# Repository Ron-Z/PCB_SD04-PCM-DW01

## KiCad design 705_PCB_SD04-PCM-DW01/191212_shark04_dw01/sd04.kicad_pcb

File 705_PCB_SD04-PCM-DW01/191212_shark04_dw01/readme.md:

### Change log

v0.1 Draft release

v0.2 - 20200316

- 根据需求增加了 均衡指示灯
- 修改了部分不合理的布线。

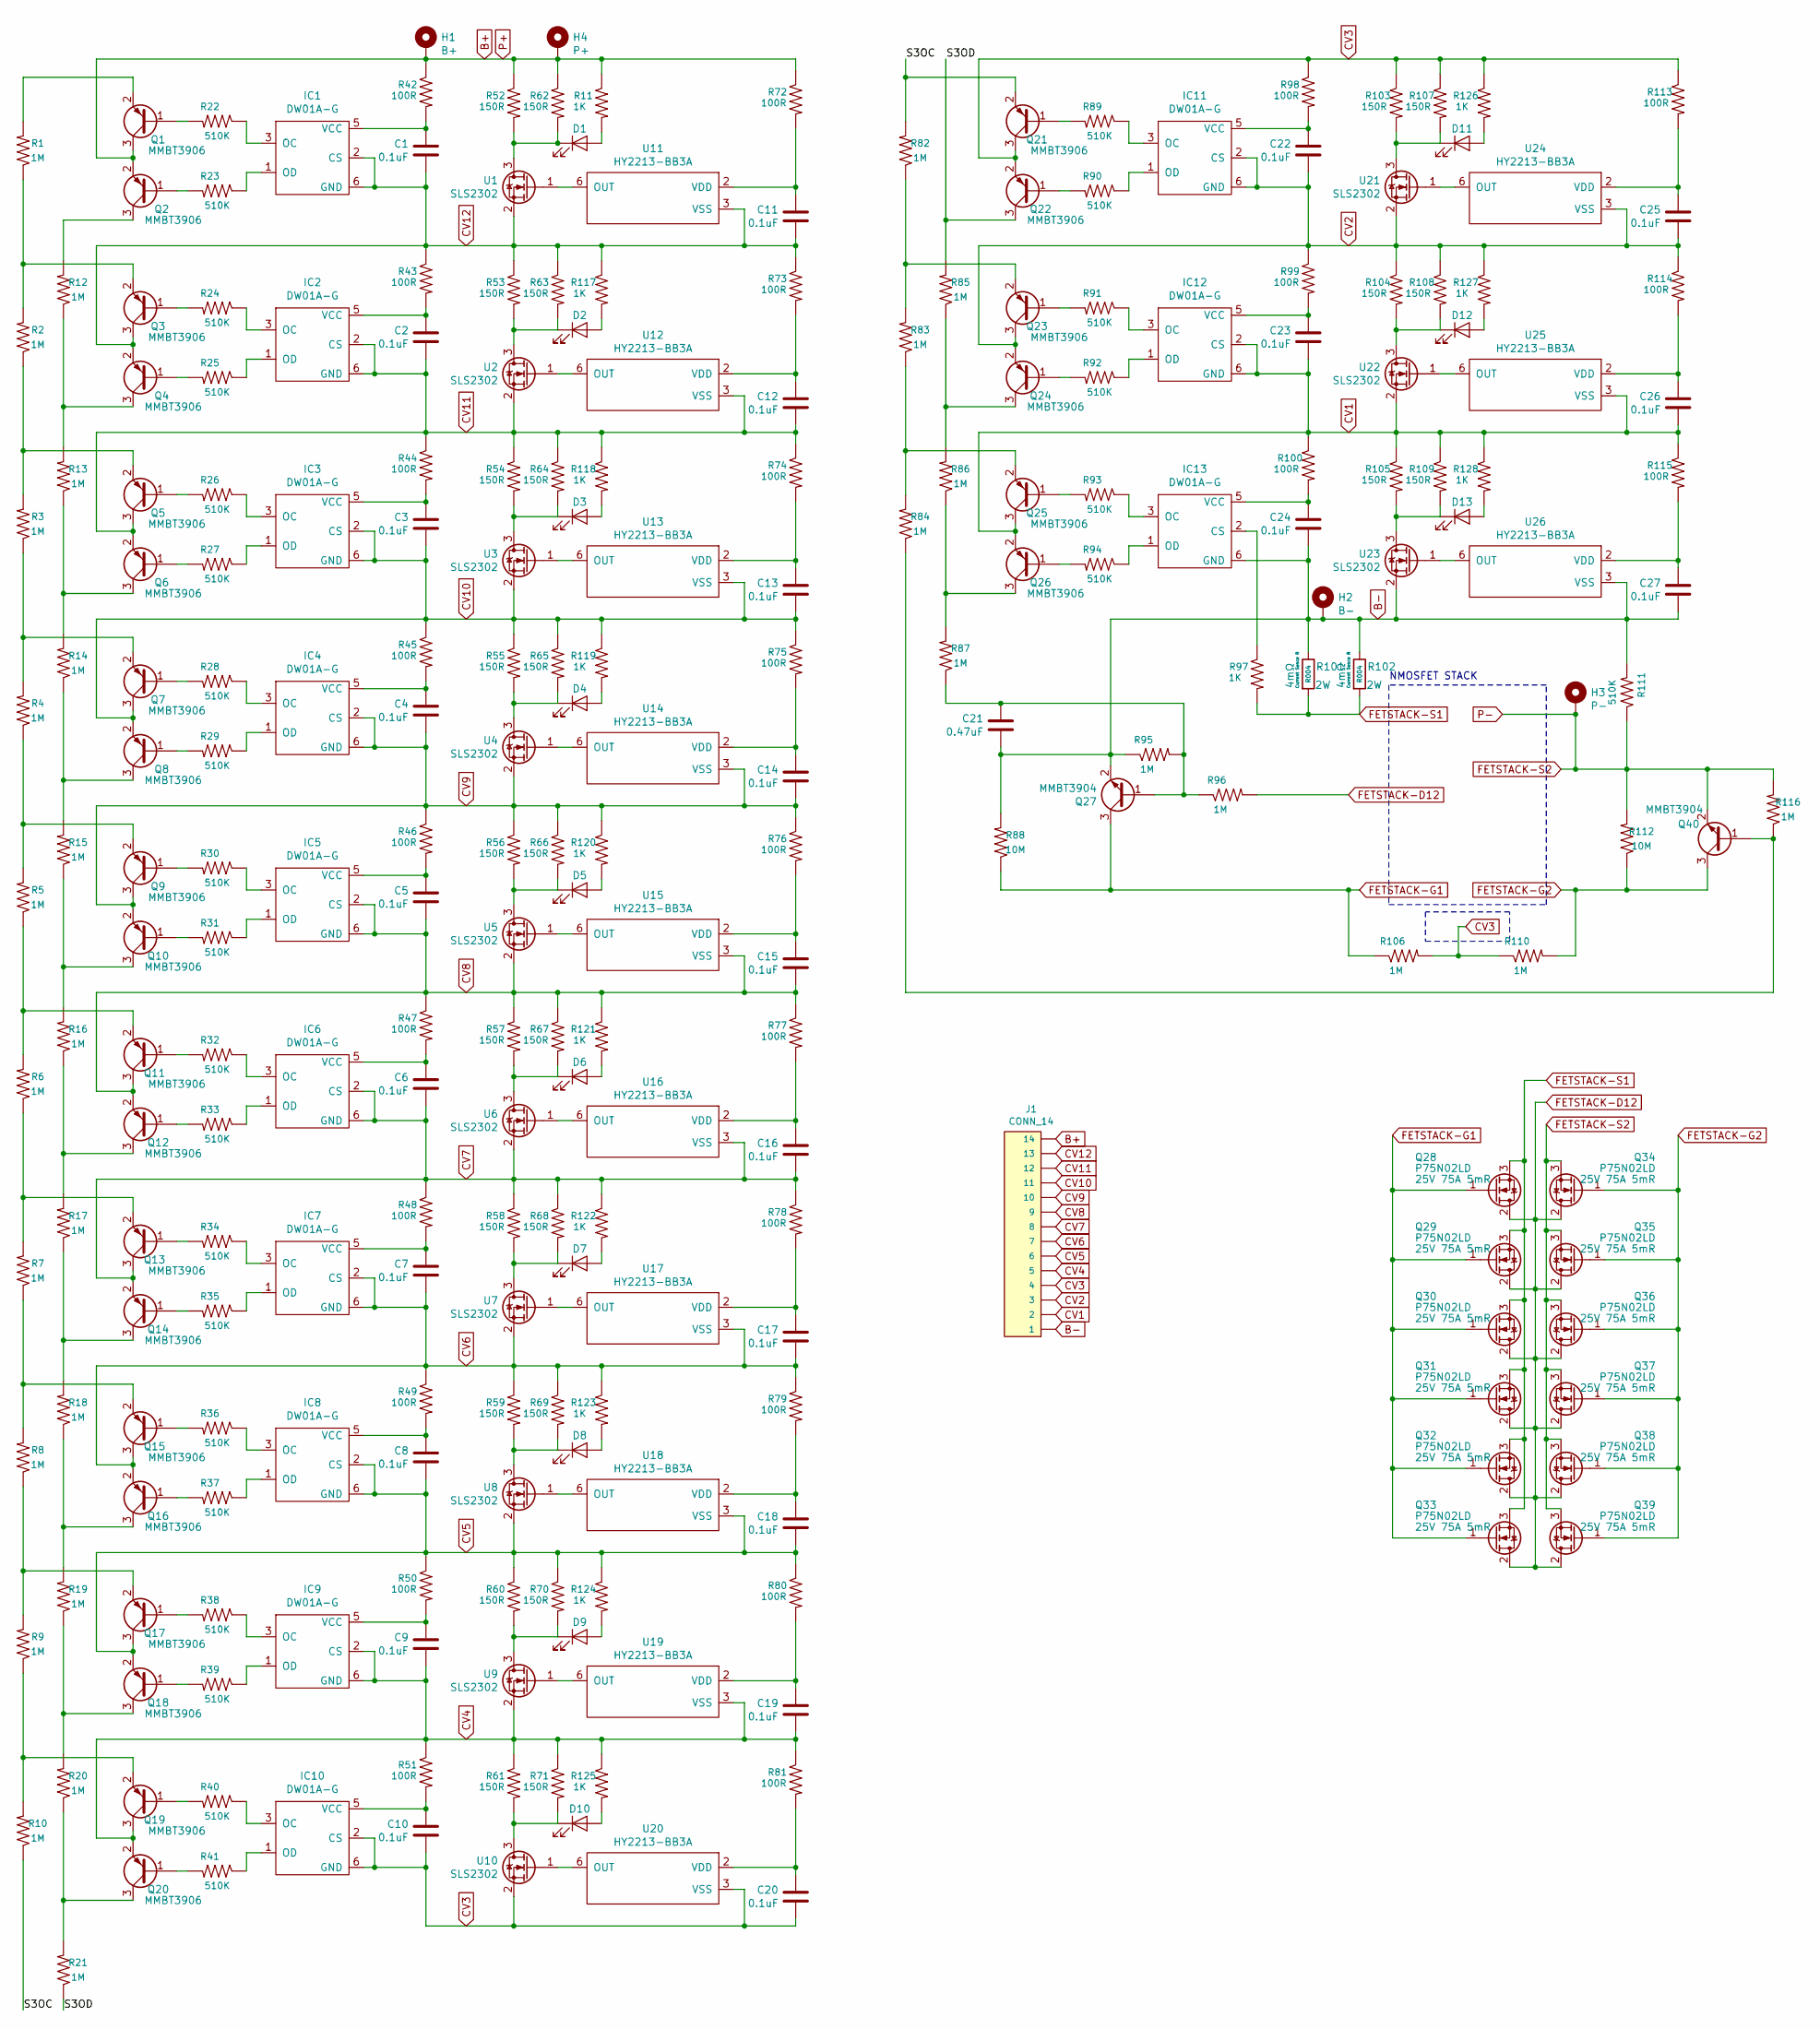
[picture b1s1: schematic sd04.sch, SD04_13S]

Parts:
C1, C2, C3, C4, C5, C6, C7, C8, C9, C10, C11, C12, C13, C14, C15, C16, C17, C18, C19, C20, C22, C23, C24, C25, C26, C27: 0.1uF; C_0603_1608Metric_Pad1.05x0.95mm_HandSolder
C21: 0.47uF; C_0603_1608Metric_Pad1.05x0.95mm_HandSolder
D1, D2, D3, D4, D5, D6, D7, D8, D9, D10, D11, D12, D13: LED; LED_0603_1608Metric_Pad1.05x0.95mm_HandSolder
H1: B+; SolderWirePad_1x01_SMD_5x5mm
H2: B-; SolderWirePad_1x01_SMD_5x5mm
H3: P-; SolderWirePad_1x01_SMD_5x5mm
H4: P+; SolderWirePad_1x01_SMD_5x5mm
IC1, IC2, IC3, IC4, IC5, IC6, IC7, IC8, IC9, IC10, IC11, IC12, IC13: DW01A-G; SOT-23-6_Handsoldering
J1: CONN_14; PinHeader_1x14_P2.54mm_Vertical
Q1, Q2, Q3, Q4, Q5, Q6, Q7, Q8, Q9, Q10, Q11, Q12, Q13, Q14, Q15, Q16, Q17, Q18, Q19, Q20, Q21, Q22, Q23, Q24, Q25, Q26: MMBT3906; SOT-23
Q27, Q40: MMBT3904; SOT-23
Q28, Q29, Q30, Q31, Q32, Q33, Q34, Q35, Q36, Q37, Q38, Q39: P75N02LD; TO-252-2
R1, R2, R3, R4, R5, R6, R7, R8, R9, R10, R12, R13, R14, R15, R16, R17, R18, R19, R20, R21, R82, R83, R84, R85, R86, R87, R95, R96, R106, R110, R116: 1M; R_0603_1608Metric_Pad1.05x0.95mm_HandSolder
R11, R97, R117, R118, R119, R120, R121, R122, R123, R124, R125, R126, R127, R128: 1K; R_0603_1608Metric_Pad1.05x0.95mm_HandSolder
R22, R23, R24, R25, R26, R27, R28, R29, R30, R31, R32, R33, R34, R35, R36, R37, R38, R39, R40, R41, R89, R90, R91, R92, R93, R94, R111: 510K; R_0603_1608Metric_Pad1.05x0.95mm_HandSolder
R42, R43, R44, R45, R46, R47, R48, R49, R50, R51, R72, R73, R74, R75, R76, R77, R78, R79, R80, R81, R98, R99, R100, R113, R114, R115: 100R; R_0603_1608Metric_Pad1.05x0.95mm_HandSolder
R52, R53, R54, R55, R56, R57, R58, R59, R60, R61, R62, R63, R64, R65, R66, R67, R68, R69, R70, R71, R103, R104, R105, R107, R108, R109: 150R; R_1206_3216Metric_Pad1.42x1.75mm_HandSolder
R88, R112: 10M; R_0603_1608Metric_Pad1.05x0.95mm_HandSolder
R101, R102: 4mΩ; R_2512_6332Metric_Pad1.52x3.35mm_HandSolder
U1, U2, U3, U4, U5, U6, U7, U8, U9, U10, U21, U22, U23: SLS2302; SOT-23
U11, U12, U13, U14, U15, U16, U17, U18, U19, U20, U24, U25, U26: HY2213-BB3A; SOT-23-6_Handsoldering

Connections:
/S3OC: Q21.2 (E), R10.1, R82.2
/S3OD: Q22.3 (C), R21.1, R85.2
B+: H1.1, H4.1, J1.14, Q1.3 (C), Q2.2 (E), R11.1, R42.1, R52.1, R62.1, R72.1
B-: C21.2, C24.2, C27.2, H2.1, IC13.6 (GND), J1.1, Q27.2 (E), R88.2, R95.1, R101.1, R102.1, R111.2, U23.2 (S), U26.3 (VSS)
CV1: C23.2, C26.2, IC12.2 (CS), IC12.6 (GND), J1.2, Q25.3 (C), Q26.2 (E), R100.1, R105.1, R109.1, R115.1, R128.1, U22.2 (S), U25.3 (VSS)
CV2: C22.2, C25.2, IC11.2 (CS), IC11.6 (GND), J1.3, Q23.3 (C), Q24.2 (E), R99.1, R104.1, R108.1, R114.1, R127.1, U21.2 (S), U24.3 (VSS)
CV3: C10.2, C20.2, IC10.2 (CS), IC10.6 (GND), J1.4, Q21.3 (C), Q22.2 (E), R98.1, R103.1, R106.2, R107.1, R110.1, R113.1, R126.1, U10.2 (S), U20.3 (VSS)
CV4: C9.2, C19.2, IC9.2 (CS), IC9.6 (GND), J1.5, Q19.3 (C), Q20.2 (E), R51.1, R61.1, R71.1, R81.1, R125.1, U9.2 (S), U19.3 (VSS)
CV5: C8.2, C18.2, IC8.2 (CS), IC8.6 (GND), J1.6, Q17.3 (C), Q18.2 (E), R50.1, R60.1, R70.1, R80.1, R124.1, U8.2 (S), U18.3 (VSS)
CV6: C7.2, C17.2, IC7.2 (CS), IC7.6 (GND), J1.7, Q15.3 (C), Q16.2 (E), R49.1, R59.1, R69.1, R79.1, R123.1, U7.2 (S), U17.3 (VSS)
CV7: C6.2, C16.2, IC6.2 (CS), IC6.6 (GND), J1.8, Q13.3 (C), Q14.2 (E), R48.1, R58.1, R68.1, R78.1, R122.1, U6.2 (S), U16.3 (VSS)
CV8: C5.2, C15.2, IC5.2 (CS), IC5.6 (GND), J1.9, Q11.3 (C), Q12.2 (E), R47.1, R57.1, R67.1, R77.1, R121.1, U5.2 (S), U15.3 (VSS)
CV9: C4.2, C14.2, IC4.2 (CS), IC4.6 (GND), J1.10, Q9.3 (C), Q10.2 (E), R46.1, R56.1, R66.1, R76.1, R120.1, U4.2 (S), U14.3 (VSS)
CV10: C3.2, C13.2, IC3.2 (CS), IC3.6 (GND), J1.11, Q7.3 (C), Q8.2 (E), R45.1, R55.1, R65.1, R75.1, R119.1, U3.2 (S), U13.3 (VSS)
CV11: C2.2, C12.2, IC2.2 (CS), IC2.6 (GND), J1.12, Q5.3 (C), Q6.2 (E), R44.1, R54.1, R64.1, R74.1, R118.1, U2.2 (S), U12.3 (VSS)
CV12: C1.2, C11.2, IC1.2 (CS), IC1.6 (GND), J1.13, Q3.3 (C), Q4.2 (E), R43.1, R53.1, R63.1, R73.1, R117.1, U1.2 (S), U11.3 (VSS)
FETSTACK-D12: Q28.2 (D), Q29.2 (D), Q30.2 (D), Q31.2 (D), Q32.2 (D), Q33.2 (D), Q34.2 (D), Q35.2 (D), Q36.2 (D), Q37.2 (D), Q38.2 (D), Q39.2 (D), R96.2
FETSTACK-G1: Q27.3 (C), Q28.1 (G), Q29.1 (G), Q30.1 (G), Q31.1 (G), Q32.1 (G), Q33.1 (G), R88.1, R106.1
FETSTACK-G2: Q34.1 (G), Q35.1 (G), Q36.1 (G), Q37.1 (G), Q38.1 (G), Q39.1 (G), Q40.3 (C), R110.2, R112.1
FETSTACK-S1: Q28.3 (S), Q29.3 (S), Q30.3 (S), Q31.3 (S), Q32.3 (S), Q33.3 (S), R97.2, R101.2, R102.2
FETSTACK-S2: H3.1, Q34.3 (S), Q35.3 (S), Q36.3 (S), Q37.3 (S), Q38.3 (S), Q39.3 (S), Q40.2 (E), R111.1, R112.2, R116.2
unnamed: C1.1, IC1.5 (VCC), R42.2
unnamed: C2.1, IC2.5 (VCC), R43.2
unnamed: C3.1, IC3.5 (VCC), R44.2
unnamed: C4.1, IC4.5 (VCC), R45.2
unnamed: C5.1, IC5.5 (VCC), R46.2
unnamed: C6.1, IC6.5 (VCC), R47.2
unnamed: C7.1, IC7.5 (VCC), R48.2
unnamed: C8.1, IC8.5 (VCC), R49.2
unnamed: C9.1, IC9.5 (VCC), R50.2
unnamed: C10.1, IC10.5 (VCC), R51.2
unnamed: C11.1, R72.2, U11.2 (VDD)
unnamed: C12.1, R73.2, U12.2 (VDD)
unnamed: C13.1, R74.2, U13.2 (VDD)
unnamed: C14.1, R75.2, U14.2 (VDD)
unnamed: C15.1, R76.2, U15.2 (VDD)
unnamed: C16.1, R77.2, U16.2 (VDD)
unnamed: C17.1, R78.2, U17.2 (VDD)
unnamed: C18.1, R79.2, U18.2 (VDD)
unnamed: C19.1, R80.2, U19.2 (VDD)
unnamed: C20.1, R81.2, U20.2 (VDD)
unnamed: C21.1, Q27.1 (B), R87.1, R95.2, R96.1
unnamed: C22.1, IC11.5 (VCC), R98.2
unnamed: C23.1, IC12.5 (VCC), R99.2
unnamed: C24.1, IC13.5 (VCC), R100.2
unnamed: C25.1, R113.2, U24.2 (VDD)
unnamed: C26.1, R114.2, U25.2 (VDD)
unnamed: C27.1, R115.2, U26.2 (VDD)
unnamed: D1.1 (K), R52.2, R62.2, U1.3 (D)
unnamed: D1.2 (A), R11.2
unnamed: D2.1 (K), R53.2, R63.2, U2.3 (D)
unnamed: D2.2 (A), R117.2
unnamed: D3.1 (K), R54.2, R64.2, U3.3 (D)
unnamed: D3.2 (A), R118.2
unnamed: D4.1 (K), R55.2, R65.2, U4.3 (D)
unnamed: D4.2 (A), R119.2
unnamed: D5.1 (K), R56.2, R66.2, U5.3 (D)
unnamed: D5.2 (A), R120.2
unnamed: D6.1 (K), R57.2, R67.2, U6.3 (D)
unnamed: D6.2 (A), R121.2
unnamed: D7.1 (K), R58.2, R68.2, U7.3 (D)
unnamed: D7.2 (A), R122.2
unnamed: D8.1 (K), R59.2, R69.2, U8.3 (D)
unnamed: D8.2 (A), R123.2
unnamed: D9.1 (K), R60.2, R70.2, U9.3 (D)
unnamed: D9.2 (A), R124.2
unnamed: D10.1 (K), R61.2, R71.2, U10.3 (D)
unnamed: D10.2 (A), R125.2
unnamed: D11.1 (K), R103.2, R107.2, U21.3 (D)
unnamed: D11.2 (A), R126.2
unnamed: D12.1 (K), R104.2, R108.2, U22.3 (D)
unnamed: D12.2 (A), R127.2
unnamed: D13.1 (K), R105.2, R109.2, U23.3 (D)
unnamed: D13.2 (A), R128.2
unnamed: IC1.1 (OD), R23.1
unnamed: IC1.3 (OC), R22.1
unnamed: IC2.1 (OD), R25.1
unnamed: IC2.3 (OC), R24.1
unnamed: IC3.1 (OD), R27.1
unnamed: IC3.3 (OC), R26.1
unnamed: IC4.1 (OD), R29.1
unnamed: IC4.3 (OC), R28.1
unnamed: IC5.1 (OD), R31.1
unnamed: IC5.3 (OC), R30.1
unnamed: IC6.1 (OD), R33.1
unnamed: IC6.3 (OC), R32.1
unnamed: IC7.1 (OD), R35.1
unnamed: IC7.3 (OC), R34.1
unnamed: IC8.1 (OD), R37.1
unnamed: IC8.3 (OC), R36.1
unnamed: IC9.1 (OD), R39.1
unnamed: IC9.3 (OC), R38.1
unnamed: IC10.1 (OD), R41.1
unnamed: IC10.3 (OC), R40.1
unnamed: IC11.1 (OD), R90.1
unnamed: IC11.3 (OC), R89.1
unnamed: IC12.1 (OD), R92.1
unnamed: IC12.3 (OC), R91.1
unnamed: IC13.1 (OD), R94.1
unnamed: IC13.2 (CS), R97.1
unnamed: IC13.3 (OC), R93.1
unnamed: Q1.1 (B), R22.2
unnamed: Q1.2 (E), R1.2
unnamed: Q2.1 (B), R23.2
unnamed: Q2.3 (C), R12.2
unnamed: Q3.1 (B), R24.2
unnamed: Q3.2 (E), R1.1, R2.2
unnamed: Q4.1 (B), R25.2
unnamed: Q4.3 (C), R12.1, R13.2
unnamed: Q5.1 (B), R26.2
unnamed: Q5.2 (E), R2.1, R3.2
unnamed: Q6.1 (B), R27.2
unnamed: Q6.3 (C), R13.1, R14.2
unnamed: Q7.1 (B), R28.2
unnamed: Q7.2 (E), R3.1, R4.2
unnamed: Q8.1 (B), R29.2
unnamed: Q8.3 (C), R14.1, R15.2
unnamed: Q9.1 (B), R30.2
unnamed: Q9.2 (E), R4.1, R5.2
unnamed: Q10.1 (B), R31.2
unnamed: Q10.3 (C), R15.1, R16.2
unnamed: Q11.1 (B), R32.2
unnamed: Q11.2 (E), R5.1, R6.2
unnamed: Q12.1 (B), R33.2
unnamed: Q12.3 (C), R16.1, R17.2
unnamed: Q13.1 (B), R34.2
unnamed: Q13.2 (E), R6.1, R7.2
unnamed: Q14.1 (B), R35.2
unnamed: Q14.3 (C), R17.1, R18.2
unnamed: Q15.1 (B), R36.2
unnamed: Q15.2 (E), R7.1, R8.2
unnamed: Q16.1 (B), R37.2
unnamed: Q16.3 (C), R18.1, R19.2
unnamed: Q17.1 (B), R38.2
unnamed: Q17.2 (E), R8.1, R9.2
unnamed: Q18.1 (B), R39.2
unnamed: Q18.3 (C), R19.1, R20.2
unnamed: Q19.1 (B), R40.2
unnamed: Q19.2 (E), R9.1, R10.2
unnamed: Q20.1 (B), R41.2
unnamed: Q20.3 (C), R20.1, R21.2
unnamed: Q21.1 (B), R89.2
unnamed: Q22.1 (B), R90.2
unnamed: Q23.1 (B), R91.2
unnamed: Q23.2 (E), R82.1, R83.2
unnamed: Q24.1 (B), R92.2
unnamed: Q24.3 (C), R85.1, R86.2
unnamed: Q25.1 (B), R93.2
unnamed: Q25.2 (E), R83.1, R84.2
unnamed: Q26.1 (B), R94.2
unnamed: Q26.3 (C), R86.1, R87.2
unnamed: Q40.1 (B), R84.1, R116.1
unnamed: U1.1 (G), U11.6 (OUT)
unnamed: U10.1 (G), U20.6 (OUT)
unnamed: U2.1 (G), U12.6 (OUT)
unnamed: U3.1 (G), U13.6 (OUT)
unnamed: U4.1 (G), U14.6 (OUT)
unnamed: U5.1 (G), U15.6 (OUT)
unnamed: U6.1 (G), U16.6 (OUT)
unnamed: U7.1 (G), U17.6 (OUT)
unnamed: U8.1 (G), U18.6 (OUT)
unnamed: U9.1 (G), U19.6 (OUT)
unnamed: U21.1 (G), U24.6 (OUT)
unnamed: U22.1 (G), U25.6 (OUT)
unnamed: U23.1 (G), U26.6 (OUT)

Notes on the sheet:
NMOSFET STACK

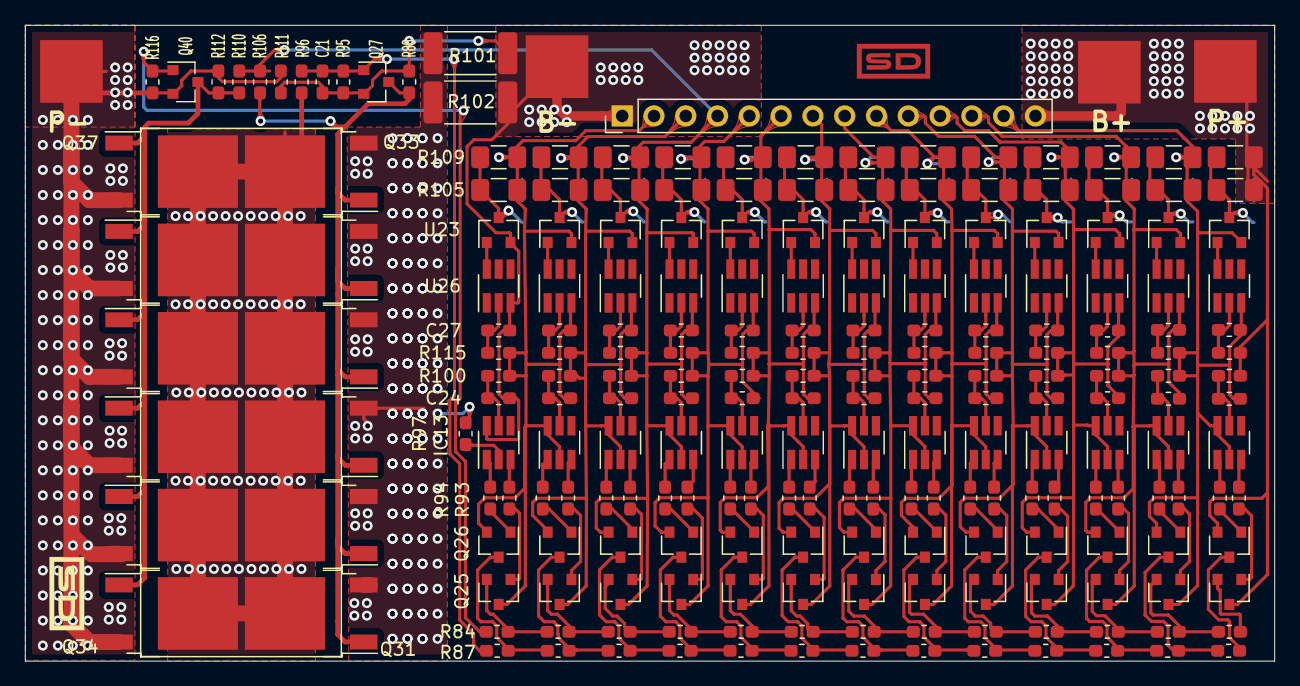
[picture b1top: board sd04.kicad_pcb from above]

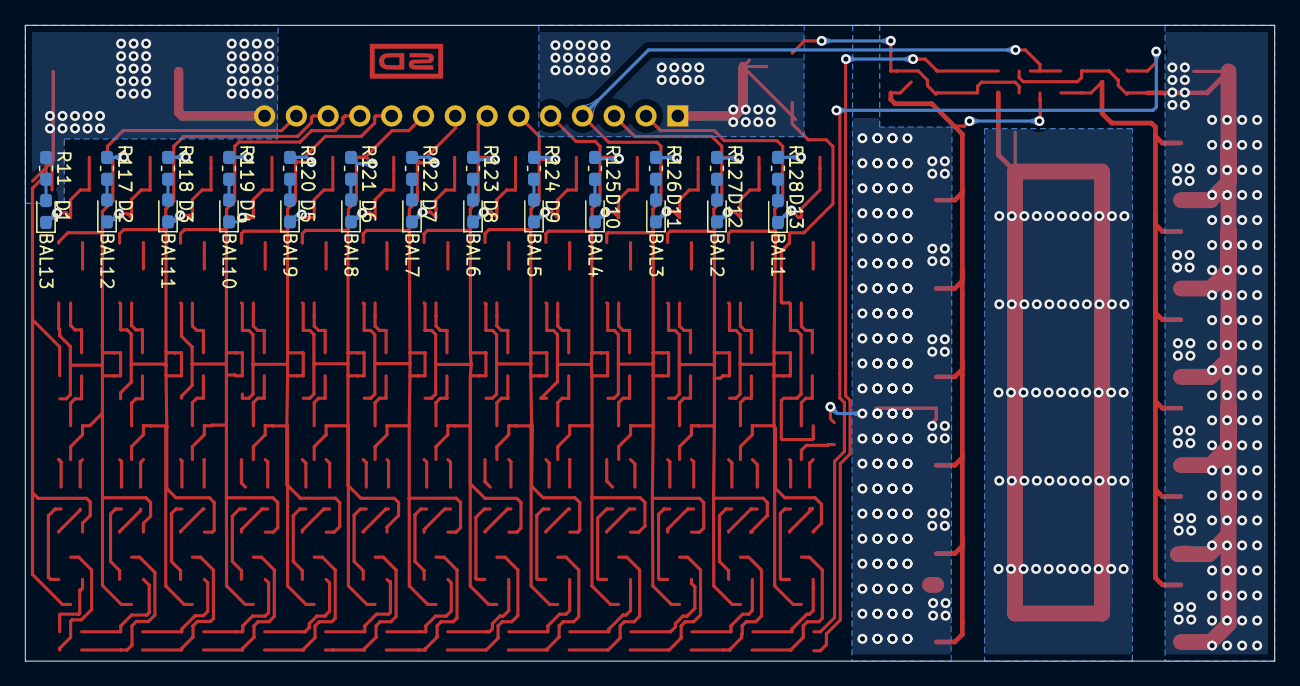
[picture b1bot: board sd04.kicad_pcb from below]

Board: 2 copper layers, 99.8 x 50.8 mm, 253 parts (26 on the bottom side), 165 nets.

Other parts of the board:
*: *; sd_logo_front_copper_with_mask
